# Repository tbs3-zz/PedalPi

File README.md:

# PedalPi
///Work in progress | unusable at the moment///
KiCad files for the PedalPi board, with a socket for the SSD1306 OLED screen and a rotary encoder to select the effect.

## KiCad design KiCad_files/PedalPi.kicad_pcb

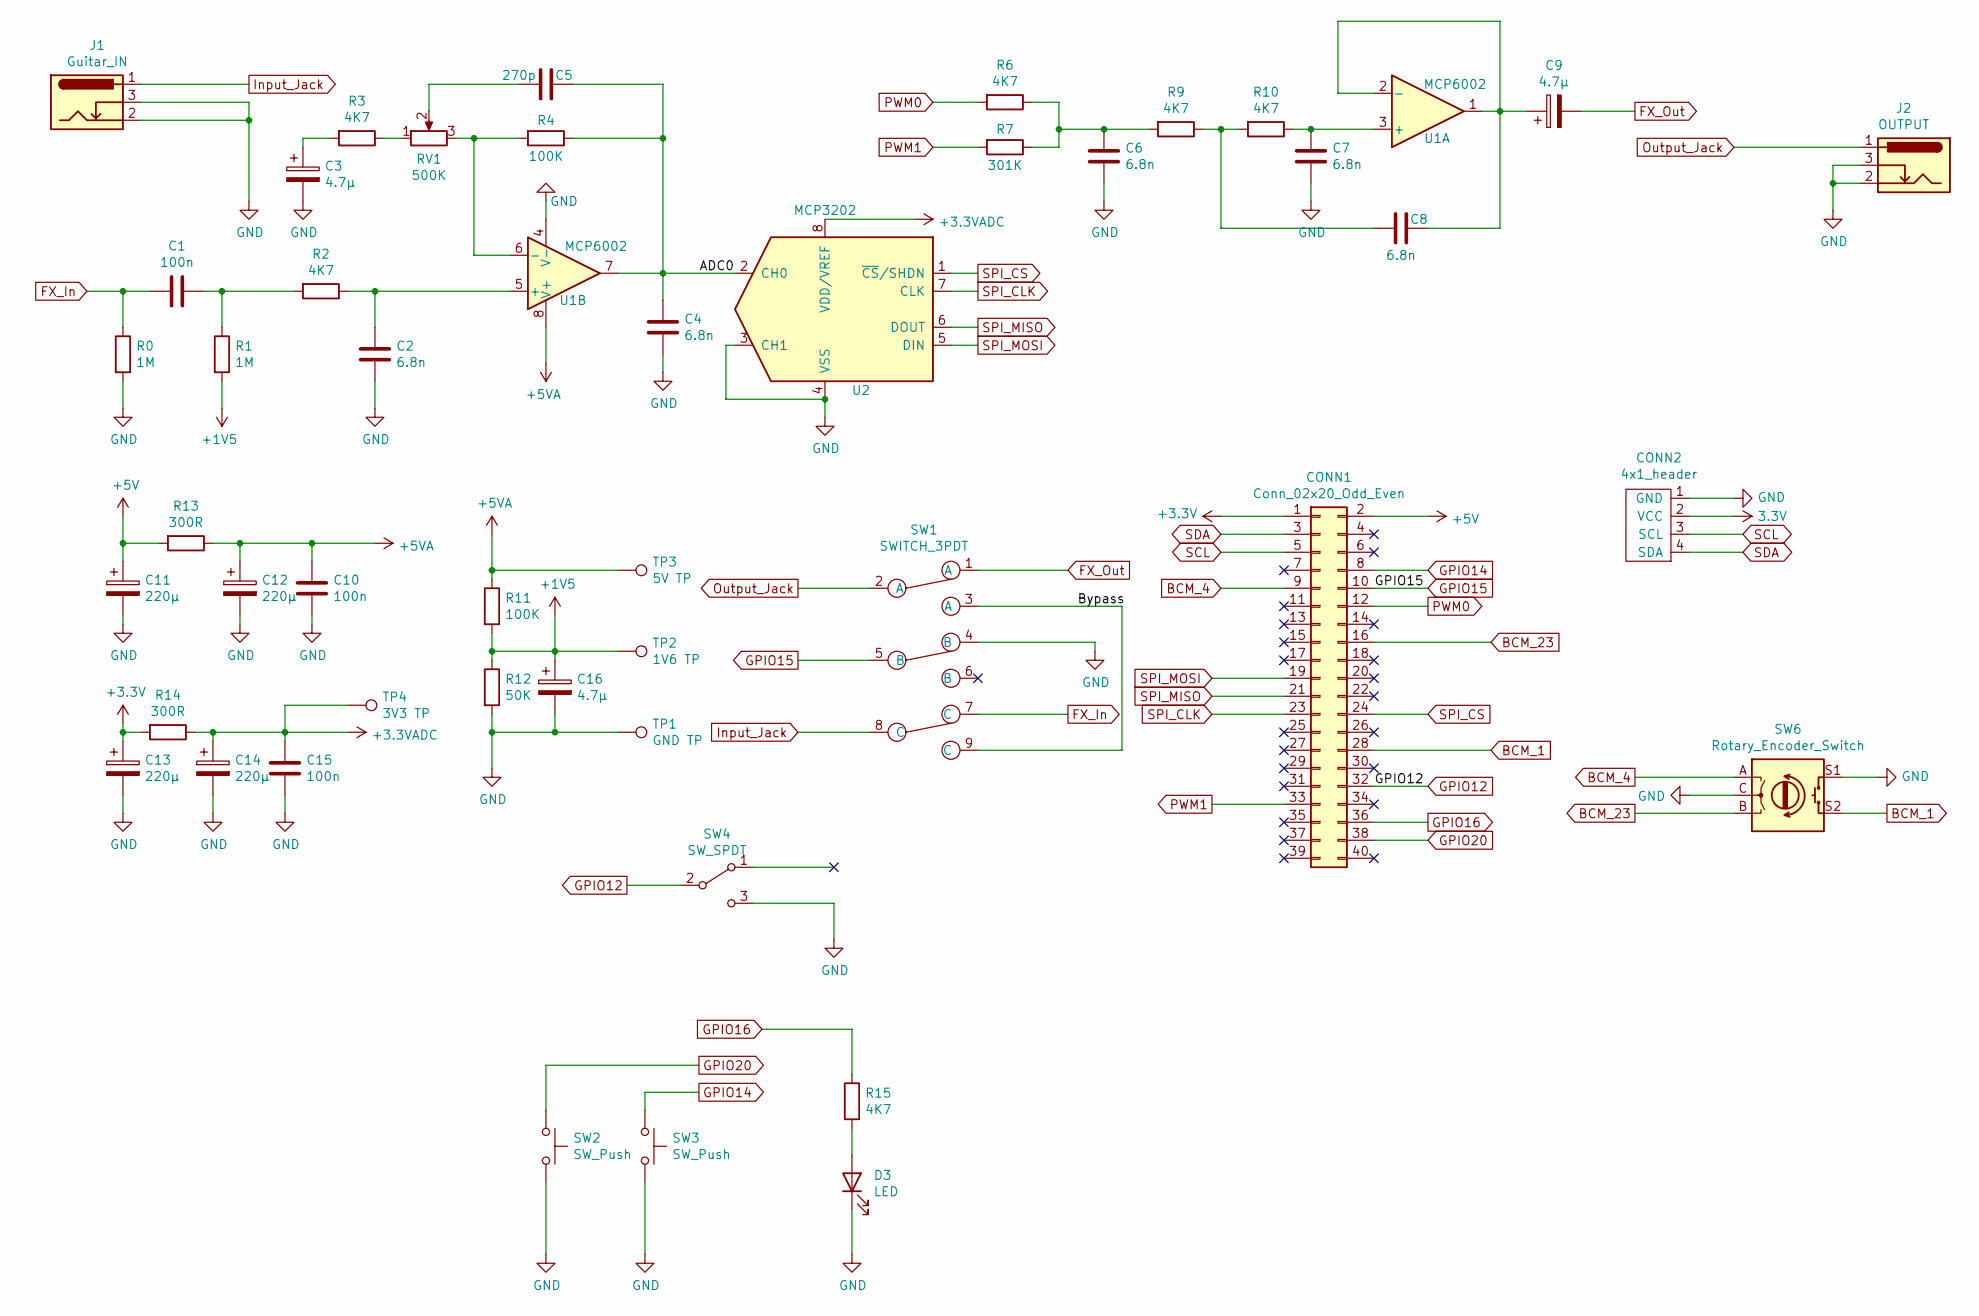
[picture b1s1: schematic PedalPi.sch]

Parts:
C1, C10, C15: 100n; SR211C104KARTR1
C2, C4, C6, C7, C8: 6.8n; SR211C682MARTR1
C3, C9, C16: 4.7µ; CAPPRD250W50D655H800
C5: 270p; C_Disc_D3.8mm_W2.6mm_P2.50mm
C11, C12, C13, C14: 220µ; CP_Radial_D8.0mm_P3.50mm
CONN1: Conn_02x20_Odd_Even; 2X20
CONN2: 4x1_header; 1X04-BIG
D3: LED; LED_D3.0mm_Clear
J1: Guitar_IN; SJ63073E
J2: OUTPUT; SJ63073E
R0, R1: 1M; R_Axial_DIN0207_L6.3mm_D2.5mm_P10.16mm_Horizontal
R2, R3, R6, R9, R10, R15: 4K7; R_Axial_DIN0207_L6.3mm_D2.5mm_P10.16mm_Horizontal
R4, R11: 100K; R_Axial_DIN0207_L6.3mm_D2.5mm_P10.16mm_Horizontal
R7: 301K; R_Axial_DIN0207_L6.3mm_D2.5mm_P10.16mm_Horizontal
R12: 50K; R_Axial_DIN0207_L6.3mm_D2.5mm_P10.16mm_Horizontal
R13, R14: 300R; R_Axial_DIN0207_L6.3mm_D2.5mm_P10.16mm_Horizontal
RV1: 500K; Potentiometer_Bourns_3386F_Vertical
SW1: SWITCH_3PDT; SF17020F030221RL015
SW2, SW3: SW_Push; SPST_SWITCH
SW4: SW_SPDT; SW_Toggle_Blue_wSlots
SW6: Rotary_Encoder_Switch; RotaryEncoder_Alps_EC11E-Switch_Vertical_H20mm
TP1: GND TP; 1X01
TP2: 1V6 TP; 1X01
TP3: 5V TP; 1X01
TP4: 3V3 TP; 1X01
U1: MCP6002; DIP-8_W7.62mm_Socket_LongPads
U2: MCP3202; DIP-8_W7.62mm_Socket_LongPads

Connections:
3.3V: CONN2.2 (VCC)
+1V5: C16.1, R1.2, R11.2, R12.1, TP2.1
+3.3VADC: C14.1, C15.1, R14.1, TP4.1, U2.8 (VDD/VREF)
+3V3: C13.1, CONN1.1, R14.2
+5V: C11.1, CONN1.2, R13.2
+5VA: C10.1, C12.1, R11.1, R13.1, TP3.1, U1.8 (V+)
/ADC0: C4.1, C5.1, R4.1, U1.7, U2.2 (CH0)
/Bypass: SW1.3 (A), SW1.9 (C)
BCM_1: CONN1.28, SW6.S2
BCM_4: CONN1.9, SW6.A
BCM_23: CONN1.16, SW6.B
FX_In: C1.2, R0.1, SW1.7 (C)
FX_Out: C9.2, SW1.1 (A)
GND: C2.2, C3.2, C4.2, C6.2, C7.2, C10.2, C11.2, C12.2, C13.2, C14.2, C15.2, C16.2, CONN2.1 (GND), D3.1 (K), J1.2, J1.3, J2.2, J2.3, R0.2, R12.2, SW1.4 (B), SW2.2, SW3.2, SW4.3 (C), SW6.C, SW6.S1, TP1.1, U1.4 (V-), U2.3 (CH1), U2.4 (VSS)
GPIO12: CONN1.32, SW4.2 (B)
GPIO14: CONN1.8, SW3.1
GPIO15: CONN1.10, SW1.5 (B)
GPIO16: CONN1.36, R15.1
GPIO20: CONN1.38, SW2.1
Input_Jack: J1.1, SW1.8 (C)
unnamed: C1.1, R1.1, R2.2
unnamed: C2.1, R2.1, U1.5 (+)
unnamed: C3.1, R3.2
unnamed: C5.2, RV1.2
unnamed: C6.1, R6.1, R7.1, R9.2
unnamed: C7.1, R10.1, U1.3 (+)
unnamed: C8.1, C9.1, U1.1, U1.2 (-)
unnamed: C8.2, R9.1, R10.2
unnamed: D3.2 (A), R15.2
unnamed: R3.1, RV1.1
unnamed: R4.2, RV1.3, U1.6 (-)
Output_Jack: J2.1, SW1.2 (A)
PWM0: CONN1.12, R6.2
PWM1: CONN1.33, R7.2
SCL: CONN1.5, CONN2.3 (SCL)
SDA: CONN1.3, CONN2.4 (SDA)
SPI_CLK: CONN1.23, U2.7 (CLK)
SPI_CS: CONN1.24, U2.1 (~CS~/SHDN)
SPI_MISO: CONN1.21, U2.6 (DOUT)
SPI_MOSI: CONN1.19, U2.5 (DIN)

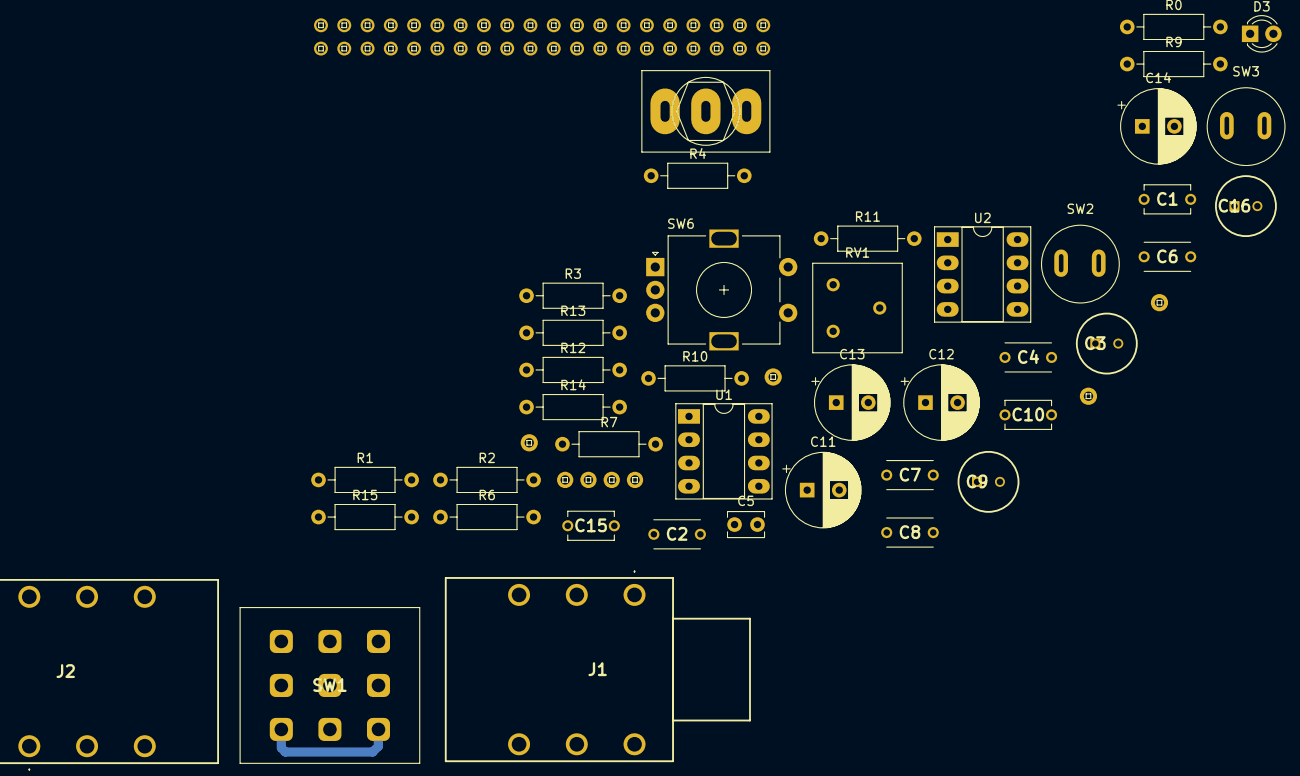
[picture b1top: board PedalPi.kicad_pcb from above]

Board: 2 copper layers, 47 parts (0 on the bottom side), 39 nets.

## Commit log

2021-05-31 Create KiCad_files
